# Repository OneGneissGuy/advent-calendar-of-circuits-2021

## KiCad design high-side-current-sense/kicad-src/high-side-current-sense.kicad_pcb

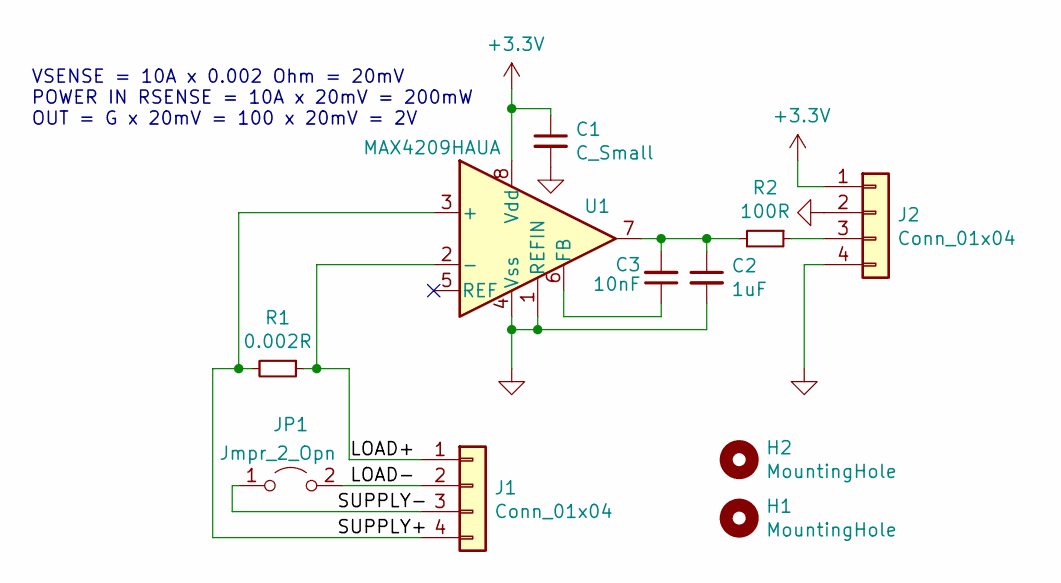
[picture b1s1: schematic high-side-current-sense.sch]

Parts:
C1: C_Small; C_0603_1608Metric
C2: 1uF; C_0603_1608Metric
C3: 10nF; C_0603_1608Metric
H1, H2: MountingHole; MountingHole_2.7mm_M2.5
J1: Conn_01x04; TerminalBlock_4Ucon_1x04_P3.50mm_Horizontal
J2: Conn_01x04; PinSocket_1x04_P2.54mm_Vertical
JP1: Jmpr_2_Opn; PinHeader_1x02_P2.54mm_Vertical
R1: 0.002R; R_1206_3216Metric
R2: 100R; R_0603_1608Metric
U1: MAX4209HAUA; MSOP-8_3x3mm_P0.65mm

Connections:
+3V3: C1.1, J2.1, U1.8 (Vdd)
/LOAD+: J1.1, R1.1, U1.2 (-)
/LOAD-: J1.2, JP1.2 (B)
/SUPPLY+: J1.4, R1.2, U1.3 (+)
/SUPPLY-: J1.3, JP1.1 (A)
GND: C1.2, C2.2, J2.2, J2.4, U1.1 (REFIN), U1.4 (Vss)
unnamed: C2.1, C3.2, R2.2, U1.7
unnamed: C3.1, U1.6 (FB)
unnamed: J2.3, R2.1

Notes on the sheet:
VSENSE = 10A x 0.002 Ohm = 20mV POWER IN RSENSE = 10A x 20mV = 200mW OUT = G x 20mV = 100 x 20mV = 2V

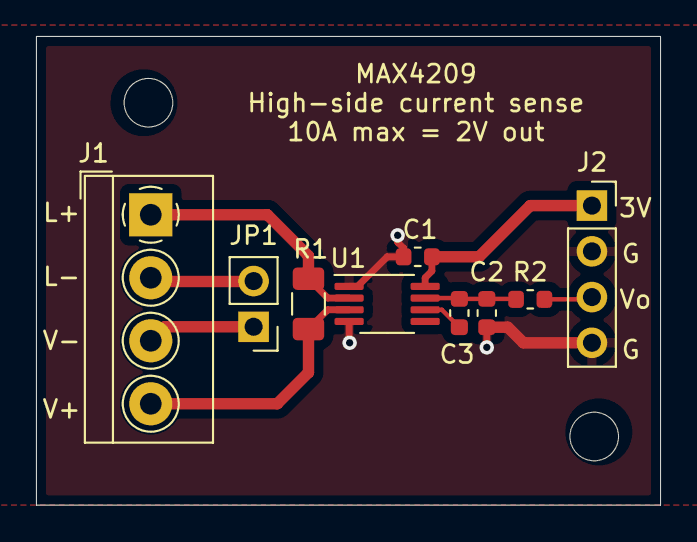
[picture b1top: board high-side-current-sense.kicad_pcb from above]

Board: 2 copper layers, 34.7 x 26.0 mm, 11 parts (0 on the bottom side), 9 nets.

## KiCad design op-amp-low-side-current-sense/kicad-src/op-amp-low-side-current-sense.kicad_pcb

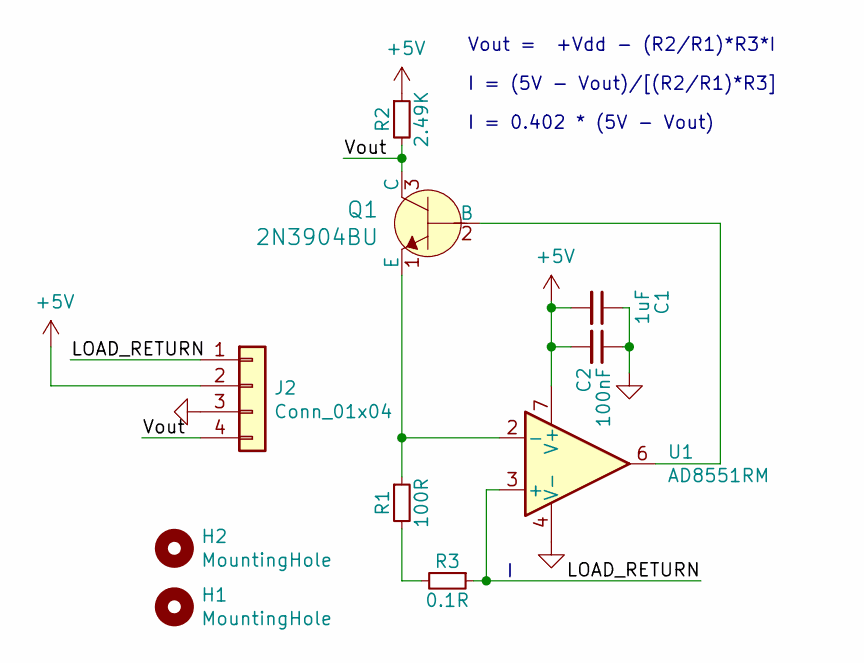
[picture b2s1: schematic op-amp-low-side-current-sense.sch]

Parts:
C1: 1uF; C_0603_1608Metric
C2: 100nF; C_0603_1608Metric
H1, H2: MountingHole; MountingHole_2.7mm_M2.5
J2: Conn_01x04; PinSocket_1x04_P2.54mm_Vertical
Q1: 2N3904BU; SOT-23-3; MPN 2N3904BU; Digi-Key_PN 2N3904FS-ND
R1: 100R; R_0603_1608Metric
R2: 2.49K; R_0603_1608Metric
R3: 0.1R; R_1206_3216Metric
U1: AD8551RM; MSOP-8_3x3mm_P0.65mm

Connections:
+5V: C1.2, C2.2, J2.2, R2.1, U1.7 (V+)
/LOAD_RETURN: J2.1, R3.1, U1.3 (+)
/Vout: J2.4, Q1.3 (C), R2.2
GND: C1.1, C2.1, J2.3, U1.4 (V-)
unnamed: Q1.1 (E), R1.1, U1.2 (-)
unnamed: Q1.2 (B), U1.6
unnamed: R1.2, R3.2

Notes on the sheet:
Vout = +Vdd - (R2/R1)*R3*I
I = (5V - Vout)/[(R2/R1)*R3]
I = 0.402 * (5V - Vout)

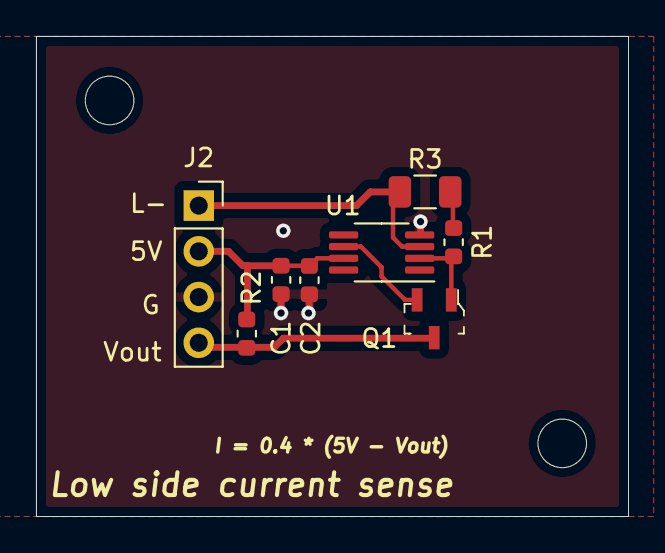
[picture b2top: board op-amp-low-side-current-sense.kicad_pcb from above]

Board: 2 copper layers, 32.9 x 26.7 mm, 10 parts (0 on the bottom side), 7 nets.

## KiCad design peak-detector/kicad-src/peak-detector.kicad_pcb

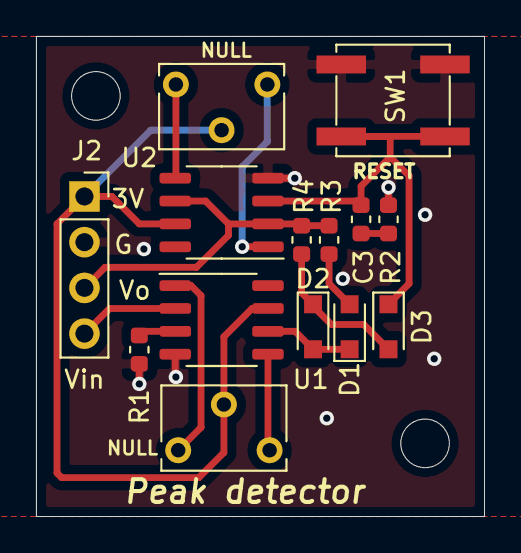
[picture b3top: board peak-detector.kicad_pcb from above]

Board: 2 copper layers, 24.9 x 26.7 mm, 16 parts (0 on the bottom side), 14 nets.

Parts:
C3: 10nF; C_0603_1608Metric
D1, D2, D3: 1N4148; D_SOD-323_HandSoldering
H1, H2: MountingHole; MountingHole_2.7mm_M2.5
J2: Conn_01x04; PinSocket_1x04_P2.54mm_Vertical
NULL: 100K; Potentiometer_Bourns_3266W_Vertical
NULL#2: 100K; Potentiometer_Bourns_3266W_Vertical
R1, R3, R4: 10K; R_0603_1608Metric
R2: 100R; R_0603_1608Metric
SW1: SW_Push; SW_SPST_EVPBF
U1, U2: TL071; SO-8_3.9x4.9mm_P1.27mm

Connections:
+3V3: J2.1, NULL.2, NULL#2.2, U1.7, U2.7
/Vin: J2.4, U1.2
/Vout: J2.3, R3.1, R4.1, U2.2, U2.6
GND: J2.2, R1.2, R2.1, SW1.2, U1.4, U2.4
unnamed: C3.1, R2.2
unnamed: C3.2, D3.1, SW1.1, U2.3
unnamed: D1.1, D2.2, U1.6
unnamed: D1.2, R3.2
unnamed: D2.1, D3.2, R4.2
unnamed: R1.1, U1.3
unnamed: NULL#2.1, U1.1
unnamed: NULL#2.3, U1.5
unnamed: NULL.1, U2.1
unnamed: NULL.3, U2.5

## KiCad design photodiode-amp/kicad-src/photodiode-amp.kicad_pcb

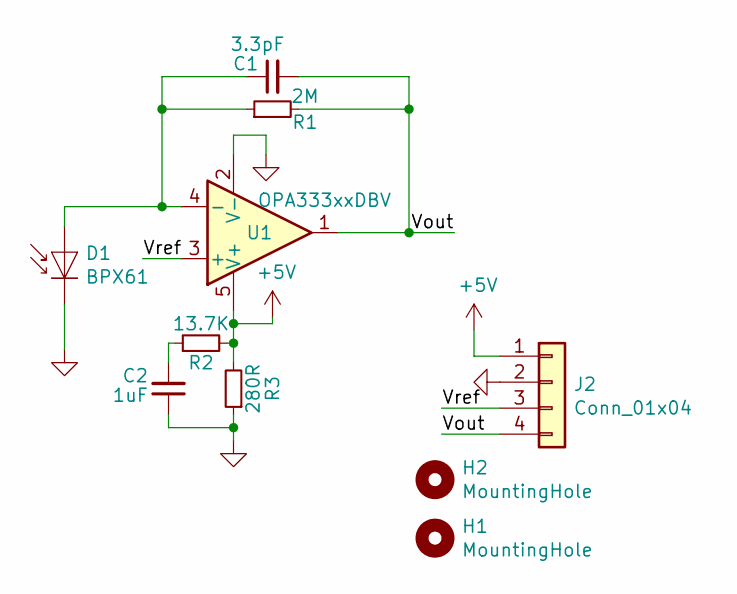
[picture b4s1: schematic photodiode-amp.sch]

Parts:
C1: 3.3pF; C_0603_1608Metric
C2: 1uF; C_0603_1608Metric
D1: BPX61; TO-5-2_Window
H1, H2: MountingHole; MountingHole_2.7mm_M2.5
J2: Conn_01x04; PinSocket_1x04_P2.54mm_Vertical
R1: 2M; R_0603_1608Metric
R2: 13.7K; R_0603_1608Metric
R3: 280R; R_0603_1608Metric
U1: OPA333xxDBV; SOT-23-5

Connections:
+5V: J2.1, R2.2, R3.2, U1.5 (V+)
/Vout: C1.2, J2.4, R1.2, U1.1
/Vref: J2.3, U1.3 (+)
GND: C2.1, D1.2 (K), J2.2, R3.1, U1.2 (V-)
unnamed: C1.1, D1.1 (A), R1.1, U1.4 (-)
unnamed: C2.2, R2.1

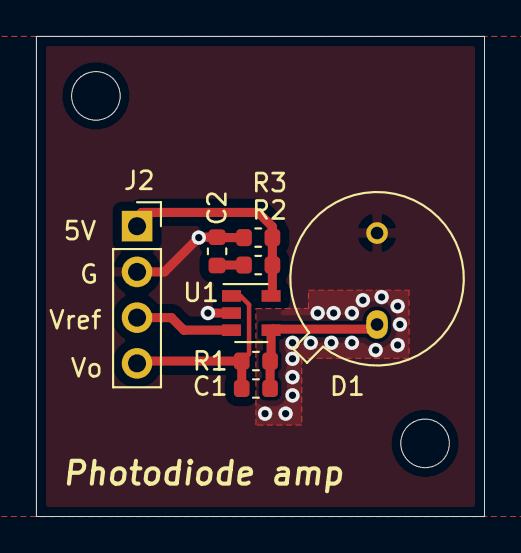
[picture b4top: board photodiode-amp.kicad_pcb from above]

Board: 2 copper layers, 24.9 x 26.7 mm, 10 parts (0 on the bottom side), 6 nets.

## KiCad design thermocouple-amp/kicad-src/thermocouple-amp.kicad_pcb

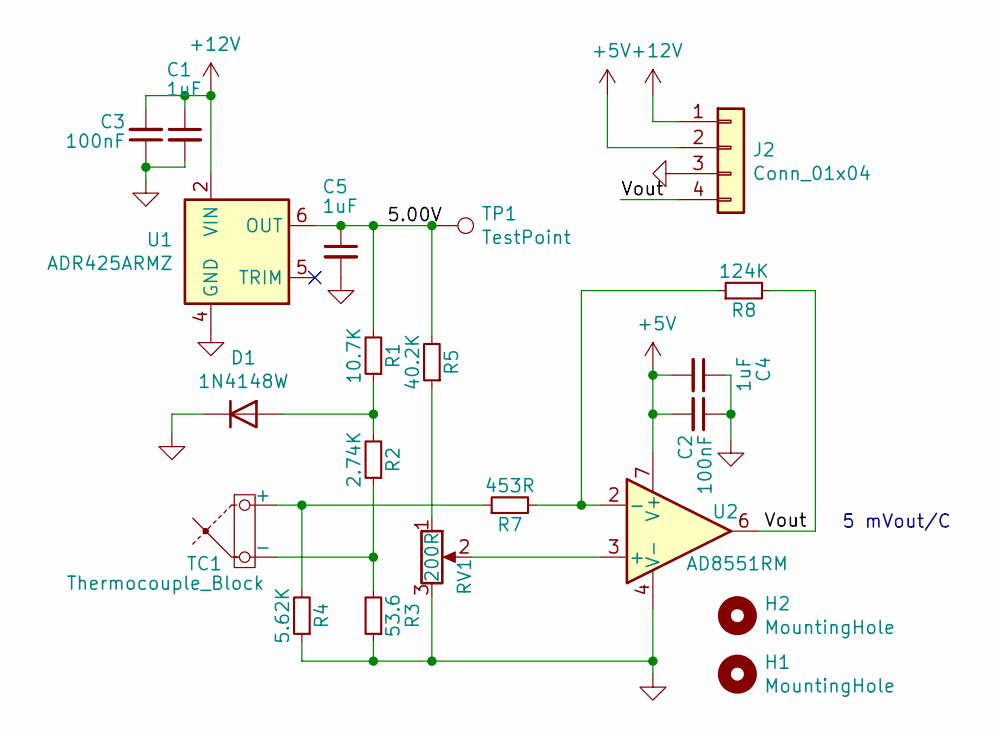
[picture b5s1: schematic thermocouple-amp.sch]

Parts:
C1, C4, C5: 1uF; C_0603_1608Metric
C2, C3: 100nF; C_0603_1608Metric
D1: 1N4148W; D_SOD-123
H1, H2: MountingHole; MountingHole_2.7mm_M2.5
J2: Conn_01x04; PinSocket_1x04_P2.54mm_Vertical
R1: 10.7K; R_0603_1608Metric
R2: 2.74K; R_0603_1608Metric
R3: 53.6; R_0603_1608Metric
R4: 5.62K; R_0603_1608Metric
R5: 40.2K; R_0603_1608Metric
R7: 453R; R_0603_1608Metric
R8: 124K; R_0603_1608Metric
RV1: 200R; Potentiometer_Bourns_3266W_Vertical
TC1: Thermocouple_Block; TerminalBlock_4Ucon_1x02_P3.50mm_Vertical
TP1: TestPoint; TestPoint_Pad_D1.0mm
U1: ADR425ARMZ; MSOP-8_3x3mm_P0.65mm
U2: AD8551RM; MSOP-8_3x3mm_P0.65mm

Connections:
+5V: C2.2, C4.2, J2.2, U2.7 (V+)
+12V: C1.1, C3.2, J2.1, U1.2 (VIN)
/5.00V: C5.1, R1.2, R5.2, TP1.1, U1.6 (OUT)
/Vout: J2.4, R8.2, U2.6
GND: C1.2, C2.1, C3.1, C4.1, C5.2, D1.1 (K), J2.3, R3.1, R4.1, RV1.3, U1.4 (GND), U2.4 (V-)
unnamed: D1.2 (A), R1.1, R2.2
unnamed: R2.1, R3.2, TC1.2 (-)
unnamed: R4.2, R7.1, TC1.1 (+)
unnamed: R5.1, RV1.1
unnamed: R7.2, R8.1, U2.2 (-)
unnamed: RV1.2, U2.3 (+)

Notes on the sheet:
5 mVout/C

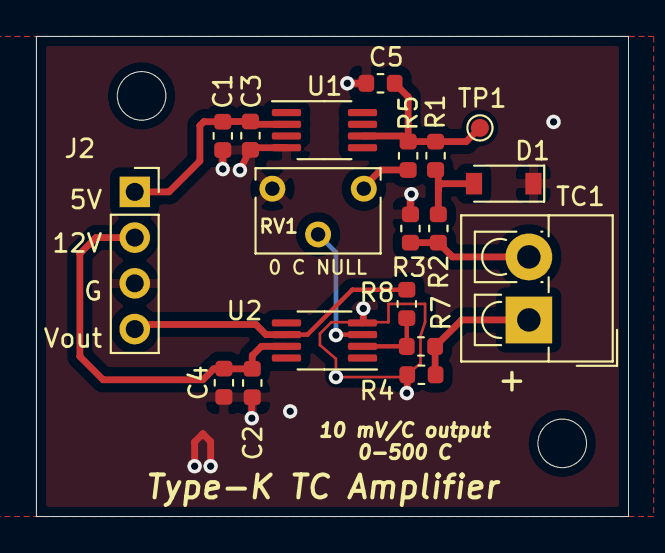
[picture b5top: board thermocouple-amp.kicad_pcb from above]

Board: 2 copper layers, 32.9 x 26.7 mm, 21 parts (0 on the bottom side), 11 nets.
